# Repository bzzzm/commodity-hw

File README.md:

# Commodity - Board

This project requires Kicad 5.1. It should include everything required to order
the board and assemble it (PCBA).

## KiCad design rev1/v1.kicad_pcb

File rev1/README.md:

# Commodity v1 - rev1

## MCU - STM32F405

  - [Datasheet](https://www.st.com/resource/en/reference_manual/dm00031020-stm32f405-415-stm32f407-417-stm32f427-437-and-stm32f429-439-advanced-arm-based-32-bit-mcus-stmicroelectronics.pdf)
  - based on Phil's design: https://www.youtube.com/watch?v=t5phi3nT8OU

## Power

### 5V Regulator - TPS62133

  - [Datasheet]()
  - [Webench design]()
  
### 3.3V LDO - AMS1117

  - [Datasheet]()

## Sensors
All sensors are connected to `I2C1` on the MCU.

### 9 Axis IMU - BMX055

  - [Datasheet](https://www.bosch-sensortec.com/media/boschsensortec/downloads/datasheets/bst-bmx055-ds000.pdf)
  - I2C addresses:
    - Accelerometer: `0x18`
    - Gyroscope: `0x68`
    - Magnetometer: `0x10`

Connected over I2C, due to some reflow issues the Magnetometer on all (that I tested) my boards is not working.

### Environment sensor - BME280

  - [Datasheet](https://ae-bst.resource.bosch.com/media/_tech/media/datasheets/BST-BME280-DS002.pdf)
  - I2C address: `0x76`

### Current sensor - INA219

  - [Datasheet](https://www.ti.com/lit/ds/symlink/ina219.pdf)
  - I2C address: `0x40`

## Peripherials

### Motor Drivers - 2 x DRV8835

  - [Datasheet](https://www.ti.com/lit/ds/symlink/drv8835.pdf)
  - `MOT_R` for right motors, `MOT_L` for left motors
    
@todo:
  - connected pins
  - PWM, max voltage etc
  - driver modes and the solder point on the back of the board

### TOF Sensors - 2 x VL53L0X

  - [Datasheet]()
  - `TOF_F` for the sensor in the front bumper
  - `TOF_T` for the sensor attached to the RPI camera
  
### Wifi Scanner - ESP8266-01
This scanner will help with positioning data (besides images from RPI cam). 
Small Arduino firmware that will scan for `N` known wifi networks every `X` seconds and will send 
the `RSSI` value via UART. The MCU will make use of DMA to receive the data on `UART2`. Firmware can be found [@todo]().

### RGB Lights - WS2812

  - [Datasheet](https://cdn-shop.adafruit.com/datasheets/WS2812B.pdf)
  - Uses SPI3 MOSI pin on the MCU to send data to the leds

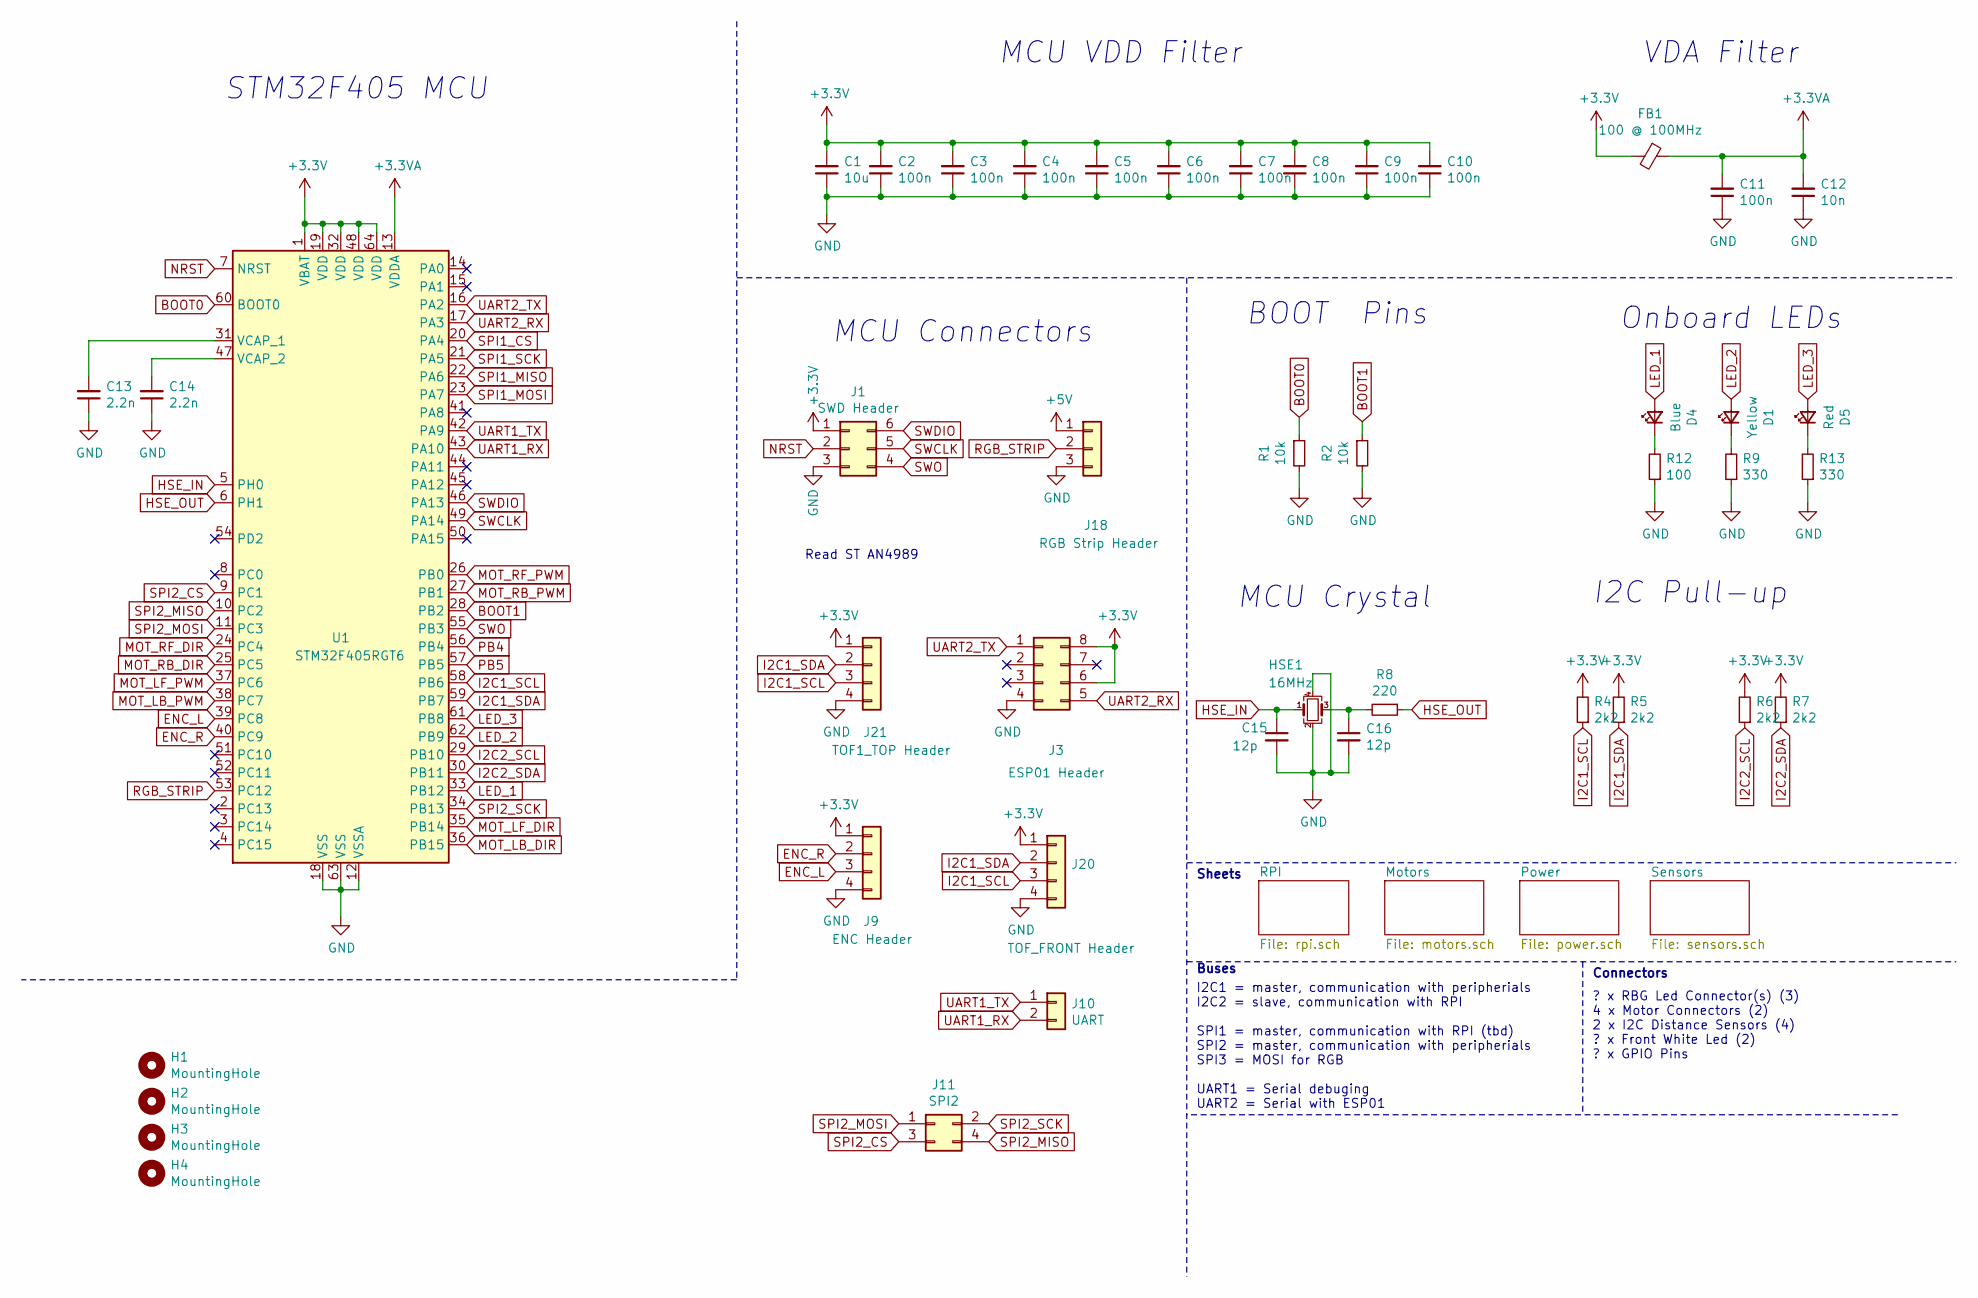
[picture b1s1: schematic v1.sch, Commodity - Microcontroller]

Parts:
C1: 10u; C_0603_1608Metric; LCSC C19702
C2, C3, C4, C5, C6, C7, C8, C9, C10, C11: 100n; C_0402_1005Metric; LCSC C1525
C12: 10n; C_0402_1005Metric; LCSC C15195
C13, C14: 2.2n; C_0603_1608Metric; LCSC C1604
C15, C16: 12p; C_0402_1005Metric; LCSC C1547
D1: Yellow; LED_0603_1608Metric; LCSC C72038
D4: Blue; LED_0603_1608Metric; LCSC C72041
D5: Red; LED_0603_1608Metric; LCSC C2286
FB1: 100 @ 100MHz; R_0805_2012Metric; LCSC C1015
H1, H2, H3, H4: MountingHole; MountingHole_2.7mm_M2.5
HSE1: 16MHz; Crystal_SMD_3225-4Pin_3.2x2.5mm; LCSC C13738
J1: SWD Header; PinHeader_2x03_P2.54mm_Vertical
J3: ESP01 Header; PinSocket_2x04_P2.54mm_Vertical
J9: ENC Header; Molex_PicoBlade_53048-0410_1x04_P1.25mm_Horizontal; Farnell 2779802
J10: UART; PinHeader_1x02_P2.54mm_Vertical
J11: SPI2; PinHeader_2x02_P2.54mm_Vertical
J18: RGB Strip Header; Molex_PicoBlade_53048-0310_1x03_P1.25mm_Horizontal; Farnell 9732918
J20: TOF_FRONT Header; Molex_PicoBlade_53048-0410_1x04_P1.25mm_Horizontal; Farnell 2779802
J21: TOF1_TOP Header; Molex_PicoBlade_53048-0410_1x04_P1.25mm_Horizontal; Farnell 2779802
R1, R2: 10k; R_0402_1005Metric; LCSC C25744
R4, R5, R6, R7: 2k2; R_0402_1005Metric; LCSC C25879
R8: 220; R_0402_1005Metric; LCSC C25091
R9, R13: 330; R_0603_1608Metric; LCSC C23138
R12: 100; R_0603_1608Metric; LCSC C22775
U1: STM32F405RGT6; LQFP-64_10x10mm_P0.5mm; LCSC C15742

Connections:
+3.3VA: C11.2, C12.2, FB1.1, U1.13 (VDDA)
BOOT0: R1.1, U1.60 (BOOT0)
BOOT1: R2.1, U1.28 (PB2)
ENC_L: J9.3, U1.39 (PC8)
ENC_R: J9.2, U1.40 (PC9)
GND: C1.1, C2.1, C3.1, C4.1, C5.1, C6.1, C7.1, C8.1, C9.1, C10.1, C11.1, C12.1, C13.1, C14.1, C15.2, C16.2, HSE1.2, HSE1.4, J1.3, J3.4, J9.4, J18.3, J20.4, J21.4, R1.2, R2.2, R9.1, R12.1, R13.1, U1.12 (VSSA), U1.18 (VSS), U1.63 (VSS); also elsewhere on the board
HSE_IN: C15.1, HSE1.1, U1.5 (PH0)
HSE_OUT: R8.1, U1.6 (PH1)
I2C1_SCL: J20.3, J21.3, R4.1, U1.58 (PB6); also elsewhere on the board
I2C1_SDA: J20.2, J21.2, R5.1, U1.59 (PB7); also elsewhere on the board
I2C2_SCL: R6.1, U1.29 (PB10); also elsewhere on the board
I2C2_SDA: R7.1, U1.30 (PB11); also elsewhere on the board
LED_1: D4.2 (A), U1.33 (PB12)
LED_2: D1.2 (A), U1.62 (PB9)
LED_3: D5.2 (A), U1.61 (PB8)
MOT_LB_DIR: U1.36 (PB15); also elsewhere on the board
MOT_LB_PWM: U1.38 (PC7); also elsewhere on the board
MOT_LF_DIR: U1.35 (PB14); also elsewhere on the board
MOT_LF_PWM: U1.37 (PC6); also elsewhere on the board
MOT_RB_DIR: U1.25 (PC5); also elsewhere on the board
MOT_RB_PWM: U1.27 (PB1); also elsewhere on the board
MOT_RF_DIR: U1.24 (PC4); also elsewhere on the board
MOT_RF_PWM: U1.26 (PB0); also elsewhere on the board
NRST: J1.2, U1.7 (NRST)
unnamed: C13.2, U1.31 (VCAP_1)
unnamed: C14.2, U1.47 (VCAP_2)
unnamed: C16.1, HSE1.3, R8.2
unnamed: D1.1 (K), R9.2
unnamed: D4.1 (K), R12.2
unnamed: D5.1 (K), R13.2
PB4: U1.56 (PB4)
PB5: U1.57 (PB5)
RGB_STRIP: J18.2, U1.53 (PC12)
SPI1_CS: U1.20 (PA4)
SPI1_MISO: U1.22 (PA6); also elsewhere on the board
SPI1_MOSI: U1.23 (PA7); also elsewhere on the board
SPI1_SCK: U1.21 (PA5); also elsewhere on the board
SPI2_CS: J11.3, U1.9 (PC1)
SPI2_MISO: J11.4, U1.10 (PC2)
SPI2_MOSI: J11.1, U1.11 (PC3)
SPI2_SCK: J11.2, U1.34 (PB13)
SWCLK: J1.5, U1.49 (PA14)
SWDIO: J1.6, U1.46 (PA13)
SWO: J1.4, U1.55 (PB3)
TPS_VOS: J18.1; also elsewhere on the board
UART1_RX: J10.2, U1.43 (PA10)
UART1_TX: J10.1, U1.42 (PA9)
UART2_RX: J3.5, U1.17 (PA3)
UART2_TX: J3.1, U1.16 (PA2)

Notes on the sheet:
I2C1 = master, communication with peripherials I2C2 = slave, communication with RPI SPI1 = master, communication with RPI (tbd) SPI2 = master, communication with peripherials SPI3 = MOSI for RGB UART1 = Serial debuging UART2 = Serial with ESP01
MCU VDD Filter
VDA Filter
BOOT Pins
MCU Crystal
MCU Connectors
I2C Pull-up
? x RBG Led Connector(s) (3) 4 x Motor Connectors (2) 2 x I2C Distance Sensors (4) ? x Front White Led (2) ? x GPIO Pins
Buses
Connectors
Sheets
Read ST AN4989
STM32F405 MCU
Onboard LEDs

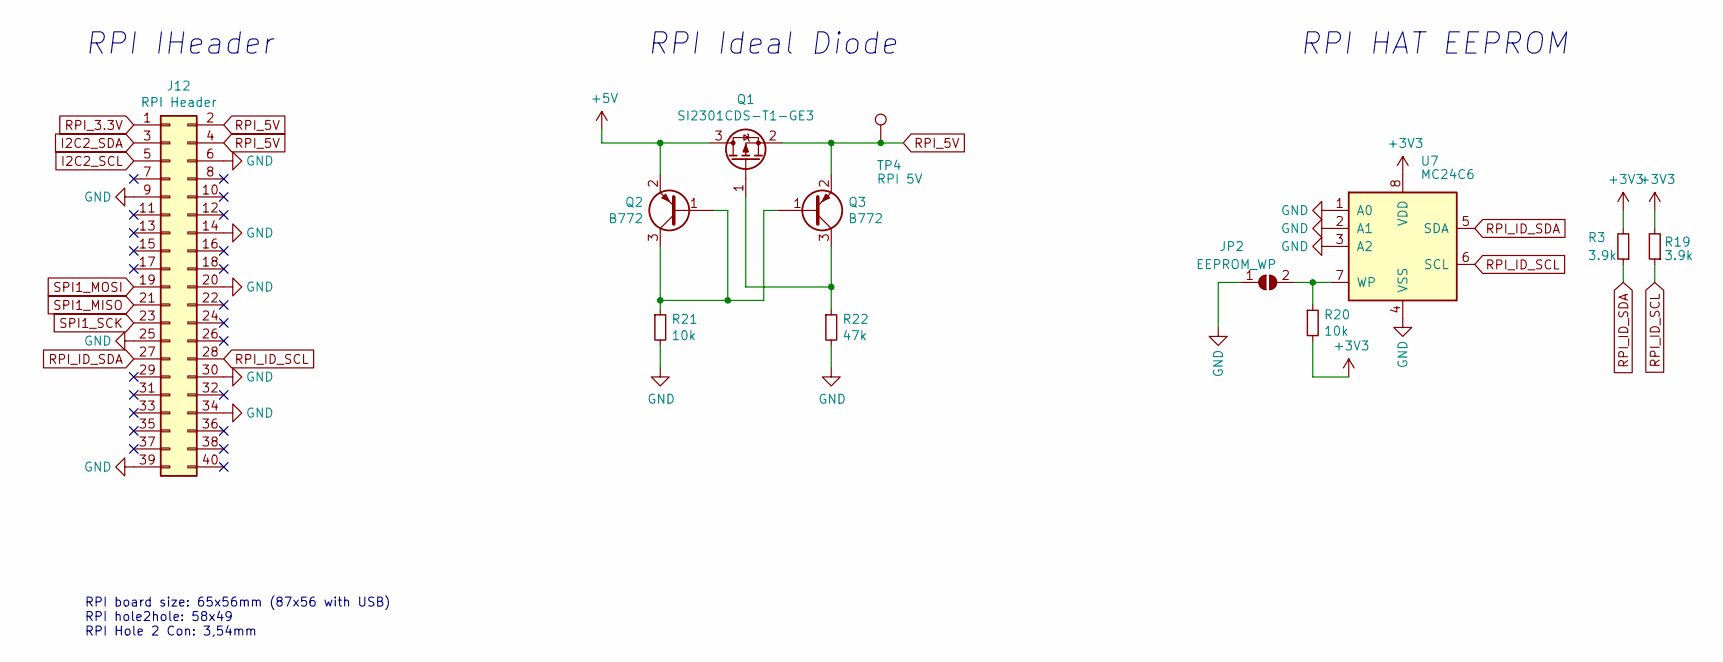
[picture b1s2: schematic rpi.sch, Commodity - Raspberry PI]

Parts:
J12: RPI Header; PinSocket_2x20_P2.54mm_Vertical
JP2: EEPROM_WP; SolderJumper-2_P1.3mm_Open_RoundedPad1.0x1.5mm
Q1: SI2301CDS-T1-GE3; SOT-23; LCSC C10487
Q2, Q3: B772; SOT-89-3; LCSC C24278
R3, R19: 3.9k; R_0402_1005Metric; LCSC C51721
R20: 10k; R_0402_1005Metric; LCSC C25744
R21: 10k; R_0603_1608Metric; LCSC C25804
R22: 47k; R_0603_1608Metric; LCSC C25819
TP4: RPI 5V; TestPoint_Pad_D1.0mm
U7: MC24C6; SOIC-8_3.9x4.9mm_P1.27mm; LCSC C79988

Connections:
GND: J12.6, J12.9, J12.14, J12.20, J12.25, J12.30, J12.34, J12.39, JP2.1 (A), R21.2, R22.2, U7.1 (A0), U7.2 (A1), U7.3 (A2), U7.4 (VSS); also elsewhere on the board
I2C2_SCL: J12.5; also elsewhere on the board
I2C2_SDA: J12.3; also elsewhere on the board
unnamed: JP2.2 (B), R20.1, U7.7 (WP)
unnamed: Q1.1 (G), Q3.3 (C), R22.1
unnamed: Q2.1 (B), Q2.3 (C), Q3.1 (B), R21.1
RPI_3.3V: J12.1
RPI_5V: J12.2, J12.4, Q1.2 (S), Q3.2 (E), TP4.1
RPI_ID_SCL: J12.28, R19.1, U7.6 (SCL)
RPI_ID_SDA: J12.27, R3.1, U7.5 (SDA)
SPI1_MISO: J12.21; also elsewhere on the board
SPI1_MOSI: J12.19; also elsewhere on the board
SPI1_SCK: J12.23; also elsewhere on the board
TPS_VOS: Q1.3 (D), Q2.2 (E); also elsewhere on the board

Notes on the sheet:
RPI board size: 65x56mm (87x56 with USB) RPI hole2hole: 58x49 RPI Hole 2 Con: 3,54mm
RPI Ideal Diode
RPI IHeader
RPI HAT EEPROM

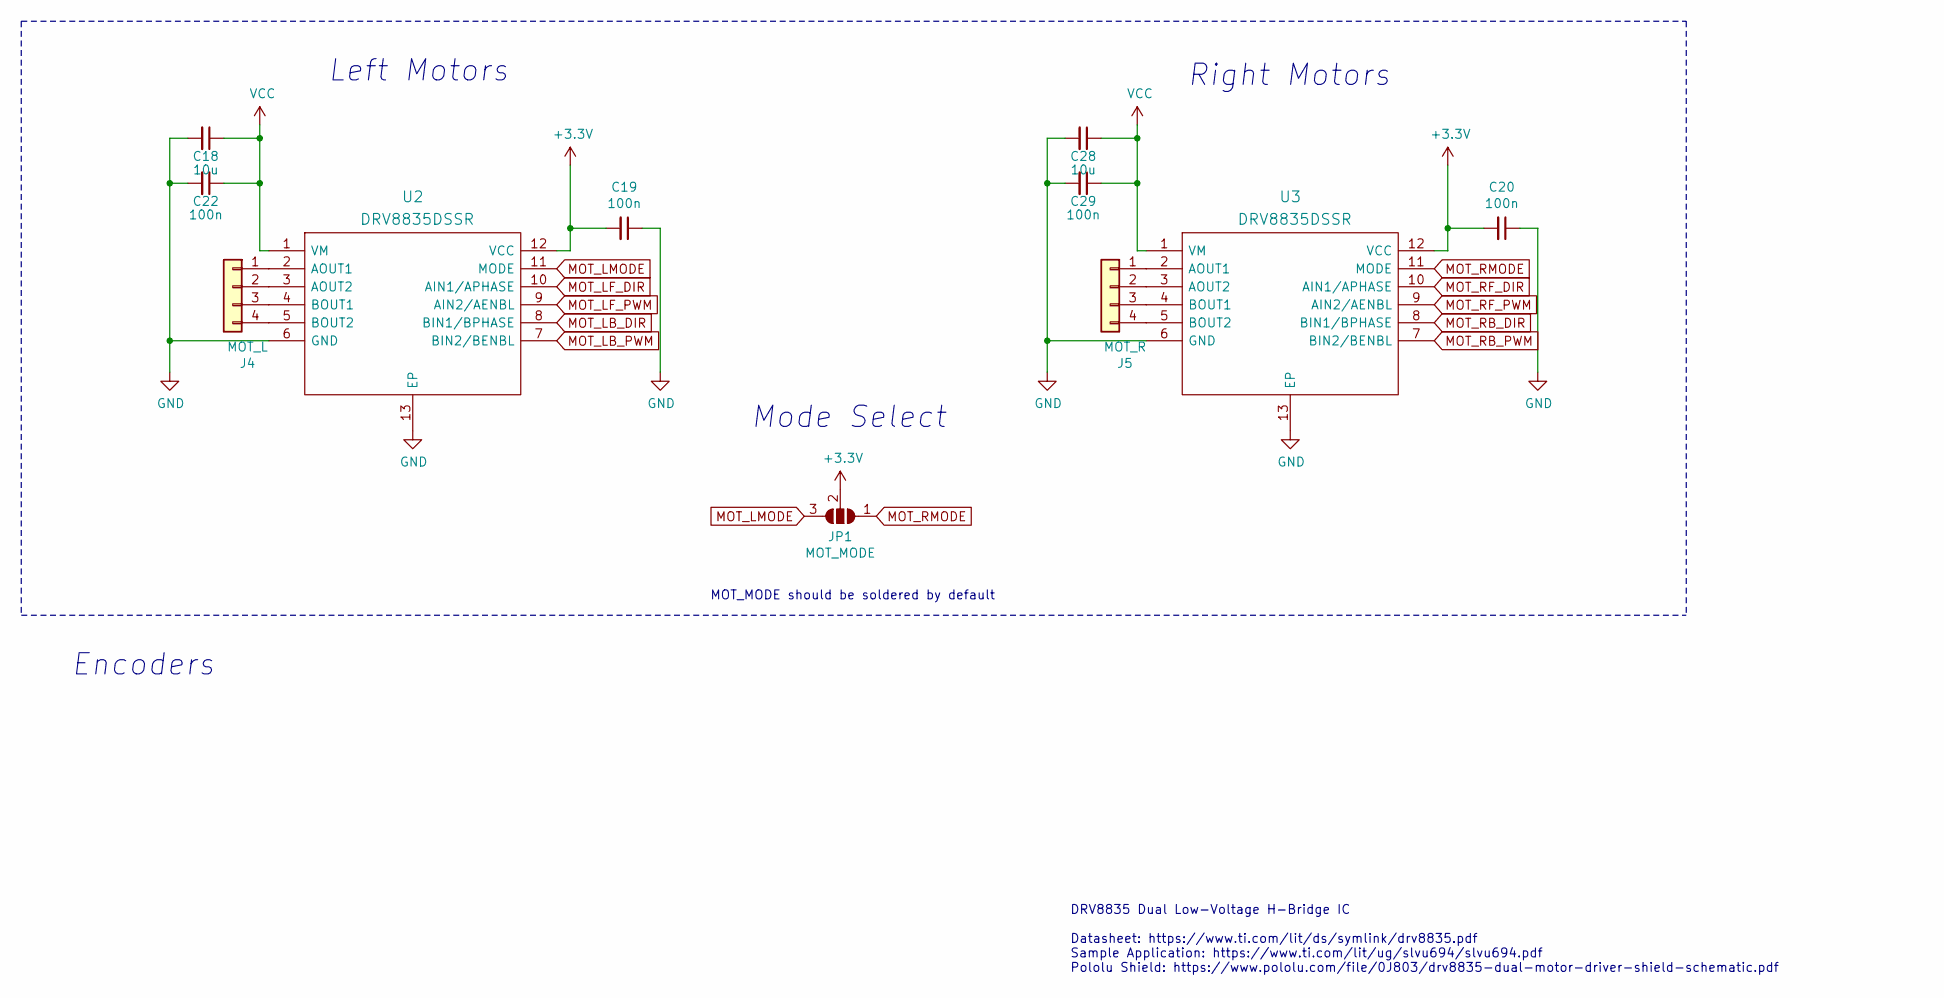
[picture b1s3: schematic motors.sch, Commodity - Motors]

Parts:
C18, C28: 10u; C_1206_3216Metric; LCSC C13585
C19, C20, C22, C29: 100n; C_0603_1608Metric; LCSC C14663
J4: MOT_L; Molex_PicoBlade_53048-0410_1x04_P1.25mm_Horizontal; Farnell 2779802
J5: MOT_R; Molex_PicoBlade_53048-0410_1x04_P1.25mm_Horizontal; Farnell 2779802
JP1: MOT_MODE; SolderJumper-3_P1.3mm_Open_RoundedPad1.0x1.5mm
U2, U3: DRV8835DSSR; SON50P200X300X80-13N; LCSC C129328

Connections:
GND: C18.2, C19.1, C20.1, C22.2, C28.2, C29.2, U2.6 (GND), U2.13 (EP), U3.6 (GND), U3.13 (EP); also elsewhere on the board
INA_VIN-: C18.1, C22.1, C28.1, C29.1, U2.1 (VM), U3.1 (VM); also elsewhere on the board
MOT_LB_DIR: U2.8 (BIN1/BPHASE); also elsewhere on the board
MOT_LB_PWM: U2.7 (BIN2/BENBL); also elsewhere on the board
MOT_LF_DIR: U2.10 (AIN1/APHASE); also elsewhere on the board
MOT_LF_PWM: U2.9 (AIN2/AENBL); also elsewhere on the board
MOT_LMODE: JP1.3 (B), U2.11 (MODE)
MOT_RB_DIR: U3.8 (BIN1/BPHASE); also elsewhere on the board
MOT_RB_PWM: U3.7 (BIN2/BENBL); also elsewhere on the board
MOT_RF_DIR: U3.10 (AIN1/APHASE); also elsewhere on the board
MOT_RF_PWM: U3.9 (AIN2/AENBL); also elsewhere on the board
MOT_RMODE: JP1.1 (A), U3.11 (MODE)
unnamed: J4.1, U2.2 (AOUT1)
unnamed: J4.2, U2.3 (AOUT2)
unnamed: J4.3, U2.4 (BOUT1)
unnamed: J4.4, U2.5 (BOUT2)
unnamed: J5.1, U3.2 (AOUT1)
unnamed: J5.2, U3.3 (AOUT2)
unnamed: J5.3, U3.4 (BOUT1)
unnamed: J5.4, U3.5 (BOUT2)

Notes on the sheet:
Right Motors
Left Motors
Encoders
DRV8835 Dual Low-Voltage H-Bridge IC Datasheet: https://www.ti.com/lit/ds/symlink/drv8835.pdf Sample Application: https://www.ti.com/lit/ug/slvu694/slvu694.pdf Pololu Shield: https://www.pololu.com/file/0J803/drv8835-dual-motor-driver-shield-schematic.pdf
Mode Select
MOT_MODE should be soldered by default

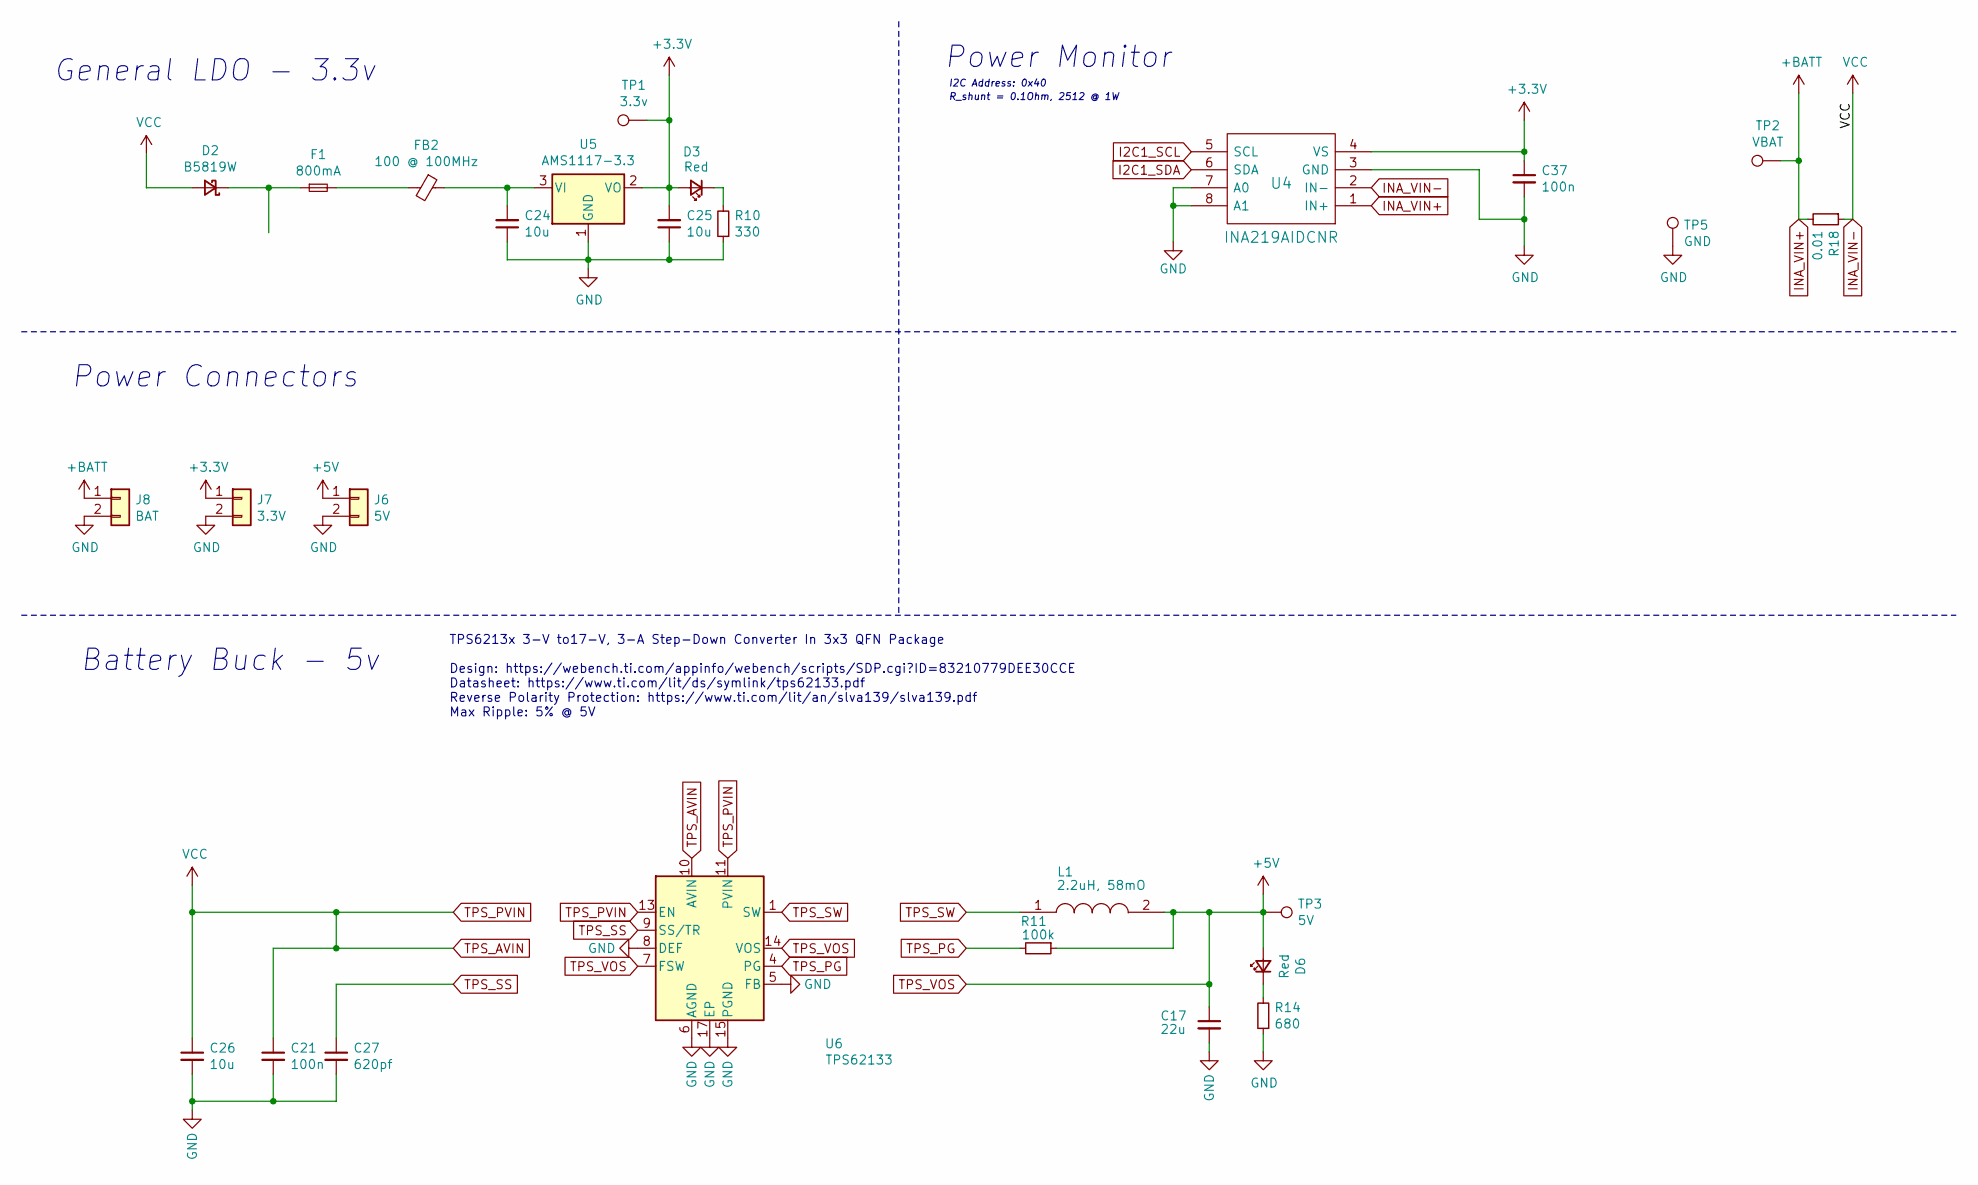
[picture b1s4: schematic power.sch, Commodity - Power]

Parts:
C17: 22u; C_0805_2012Metric; LCSC C45783
C21, C37: 100n; C_0603_1608Metric; LCSC C14663
C24, C25, C26: 10u; C_0805_2012Metric; LCSC C15850
C27: 620pf; C_0603_1608Metric_Pad1.05x0.95mm_HandSolder; Farnell 2819768
D2: B5819W; D_SOD-123; LCSC C8598
D3, D6: Red; LED_0603_1608Metric; LCSC C2286
F1: 800mA; R_1206_3216Metric_Pad1.42x1.75mm_HandSolder; Farnell 2291894
FB2: 100 @ 100MHz; R_0805_2012Metric; LCSC C1015
J6: 5V; PinHeader_1x02_P2.54mm_Vertical
J7: 3.3V; PinHeader_1x02_P2.54mm_Vertical
J8: BAT; JST_XH_S2B-XH-A_1x02_P2.50mm_Horizontal; Farnell 1516289
L1: 2.2uH, 58mO; INDPM4442X200N; LCSC C408335
R10: 330; R_0603_1608Metric; LCSC C23138
R11: 100k; R_0402_1005Metric; LCSC C25741
R14: 680; R_0603_1608Metric; LCSC C23228
R18: 0.01; R_2512_6332Metric_Pad1.52x3.35mm_HandSolder; Farnell 1435952RL
TP1: 3.3v; TestPoint_Pad_D1.0mm
TP2: VBAT; TestPoint_Pad_D1.0mm
TP3: 5V; TestPoint_Pad_D1.0mm
TP5: GND; TestPoint_Pad_D1.0mm
U4: INA219AIDCNR; SOT-23-8; LCSC C87469
U5: AMS1117-3.3; SOT-223-3_TabPin2; LCSC C6186
U6: TPS62133; VQFN-16-1EP_3x3mm_P0.5mm_EP1.68x1.68mm_ThermalVias; LCSC C73973

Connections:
GND: C17.2, C21.2, C24.1, C25.1, C26.2, C27.2, C37.2, J6.2, J7.2, J8.2, R10.1, R14.1, TP5.1, U4.3 (GND), U4.7 (A0), U4.8 (A1), U5.1 (GND), U6.5 (FB), U6.6 (AGND), U6.8 (DEF), U6.15 (PGND), U6.16 (PGND), U6.17 (EP); also elsewhere on the board
I2C1_SCL: U4.5 (SCL); also elsewhere on the board
I2C1_SDA: U4.6 (SDA); also elsewhere on the board
INA_VIN+: J8.1, R18.2, TP2.1, U4.1 (IN+)
INA_VIN-: C21.1, C26.1, D2.2 (A), R18.1, U4.2 (IN-), U6.10 (AVIN), U6.11 (PVIN), U6.12 (PVIN), U6.13 (EN); also elsewhere on the board
unnamed: C24.2, FB2.1, U5.3 (VI)
unnamed: D2.1 (K), F1.1
unnamed: D3.1 (K), R10.2
unnamed: D6.1 (K), R14.2
unnamed: F1.2, FB2.2
TPS_PG: R11.2, U6.4 (PG)
TPS_SS: C27.1, U6.9 (SS/TR)
TPS_SW: L1.1, U6.1 (SW), U6.2 (SW), U6.3 (SW)
TPS_VOS: C17.1, D6.2 (A), J6.1, L1.2, R11.1, TP3.1, U6.7 (FSW), U6.14 (VOS); also elsewhere on the board

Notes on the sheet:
Battery Buck - 5v
Power Connectors
Power Monitor
TPS6213x 3-V to17-V, 3-A Step-Down Converter In 3x3 QFN Package Design: https://webench.ti.com/appinfo/webench/scripts/SDP.cgi?ID=83210779DEE30CCE Datasheet: https://www.ti.com/lit/ds/symlink/tps62133.pdf Reverse Polarity Protection: https://www.ti.com/lit/an/slva139/slva139.pdf Max Ripple: 5% @ 5V
General LDO - 3.3v
I2C Address: 0x40
R_shunt = 0.1Ohm, 2512 @ 1W

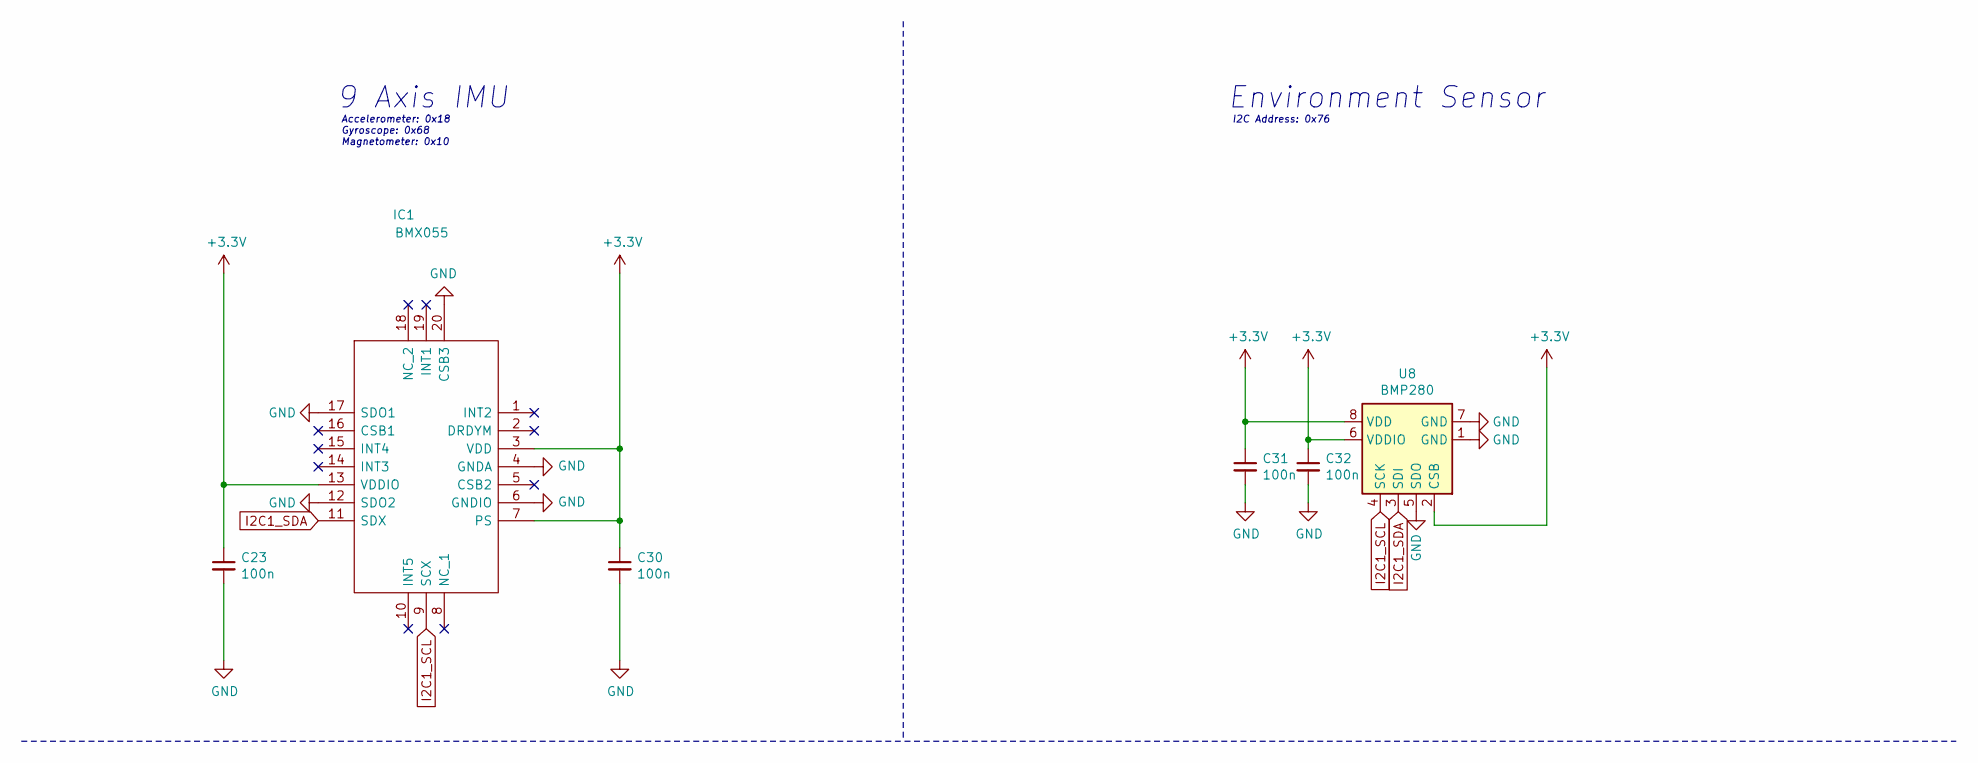
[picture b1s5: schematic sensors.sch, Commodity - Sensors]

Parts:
C23, C30, C31, C32: 100n; C_0603_1608Metric; LCSC C14663
IC1: BMX055; LGA_PACKAGE_20_PINS; Manufacturer_Part_Number BMX055; Mouser Part Number 262-BMX055
U8: BMP280; Bosch_LGA-8_2x2.5mm_P0.65mm_ClockwisePinNumbering; LCSC C83291

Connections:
GND: C23.2, C30.2, C31.2, C32.2, IC1.4 (GNDA), IC1.6 (GNDIO), IC1.12 (SDO2), IC1.17 (SDO1), IC1.20 (CSB3), U8.1 (GND), U8.5 (SDO), U8.7 (GND); also elsewhere on the board
I2C1_SCL: IC1.9 (SCX), U8.4 (SCK); also elsewhere on the board
I2C1_SDA: IC1.11 (SDX), U8.3 (SDI); also elsewhere on the board

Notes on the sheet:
Accelerometer: 0x18 Gyroscope: 0x68 Magnetometer: 0x10
9 Axis IMU
I2C Address: 0x76
Environment Sensor

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
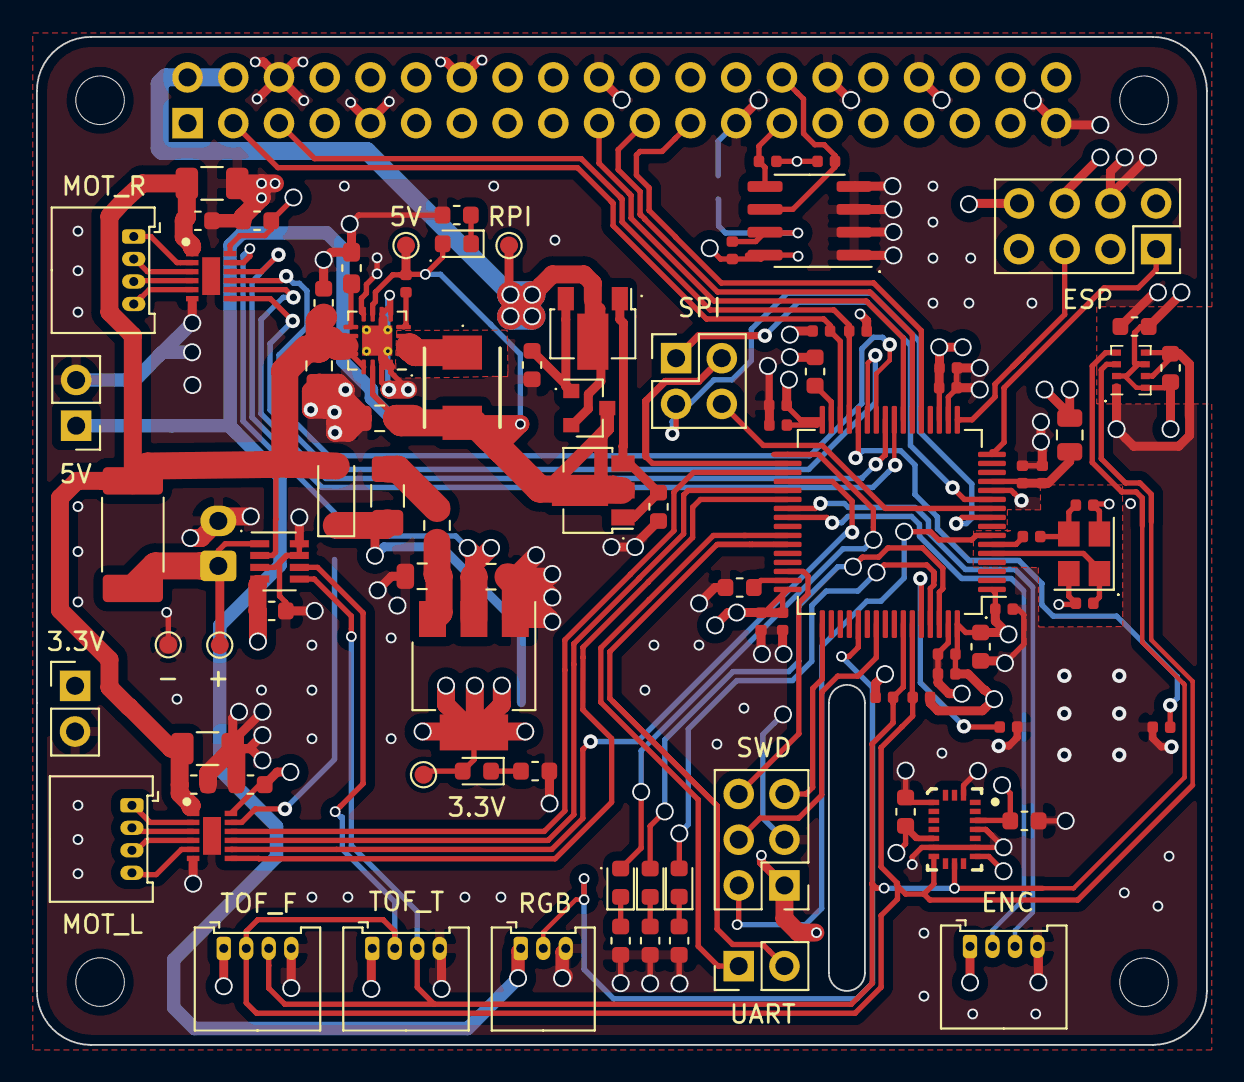
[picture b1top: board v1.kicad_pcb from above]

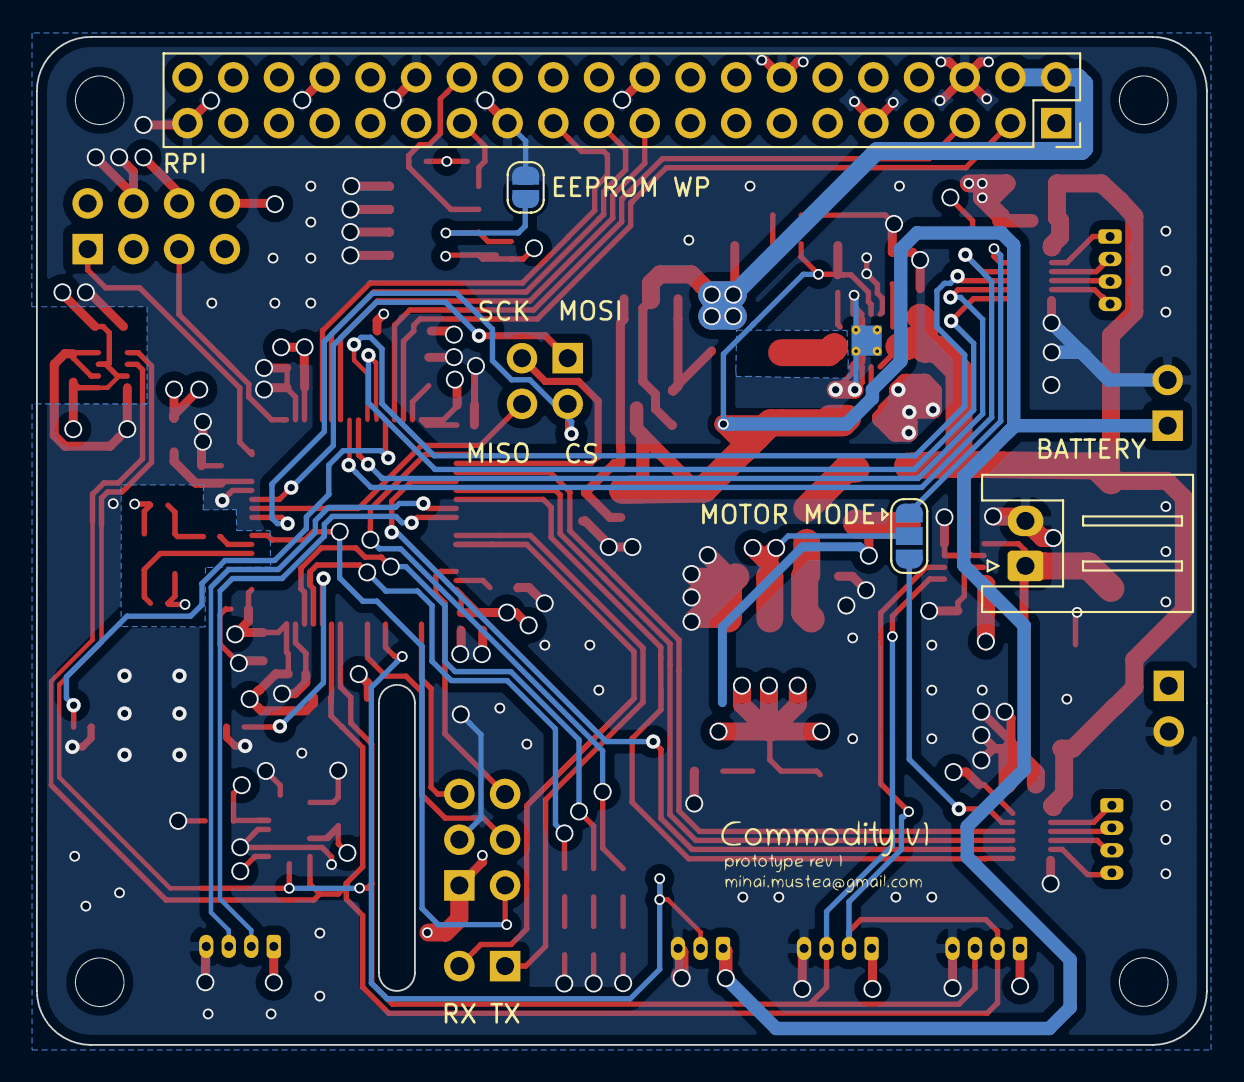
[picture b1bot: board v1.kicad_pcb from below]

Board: 4 copper layers, 65.0 x 56.0 mm, 100 parts (4 on the bottom side), 73 nets.

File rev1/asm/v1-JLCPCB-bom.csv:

Comment,Designator,Quantity,Footprint,LCSC Part #
10u,C1,1,C_0603_1608Metric,C19702
100n,"C2,C3,C4,C5,C6,C7,C8,C9,C10,C11",10,C_0402_1005Metric,C1525
10n,C12,1,C_0402_1005Metric,C15195
2.2n,"C13,C14",2,C_0603_1608Metric,C1604
12p,"C15,C16",2,C_0402_1005Metric,C1547
22u,C17,1,C_0805_2012Metric,C45783
10u,"C18,C28",2,C_1206_3216Metric,C13585
100n,"C19,C20,C21,C22,C23,C29,C30,C31,C32,C37",10,C_0603_1608Metric,C14663
10u,"C24,C25,C26",3,C_0805_2012Metric,C15850
Yellow,D1,1,LED_0603_1608Metric,C72038
B5819W,D2,1,D_SOD-123,C8598
Red,"D3,D5,D6",3,LED_0603_1608Metric,C2286
Blue,D4,1,LED_0603_1608Metric,C72041
100 @ 100MHz,"FB1,FB2",2,R_0805_2012Metric,C1015
16MHz,HSE1,1,Crystal_SMD_3225-4Pin_3.2x2.5mm,C13738
BMX055,IC1,1,LGA_PACKAGE_20_PINS,C94022
"2.2uH, 58mO",L1,1,SMD-PIND-4.2x4.4x2.0_0.8x2.0,C408335
SI2301CDS-T1-GE3,Q1,1,SOT-23,C10487
B772,"Q2,Q3",2,SOT-89-3,C24278
10k,"R1,R2,R20",3,R_0402_1005Metric,C25744
3.9k,"R3,R19",2,R_0402_1005Metric,C51721
2k2,"R4,R5,R6,R7",4,R_0402_1005Metric,C25879
220,R8,1,R_0402_1005Metric,C25091
330,"R9,R10,R13",3,R_0603_1608Metric,C23138
100k,R11,1,R_0402_1005Metric,C25741
100,R12,1,R_0603_1608Metric,C22775
680,R14,1,R_0603_1608Metric,C23228
10k,R21,1,R_0603_1608Metric,C25804
47k,R22,1,R_0603_1608Metric,C25819
STM32F405RGT6,U1,1,LQFP-64_10x10mm_P0.5mm,C15742
DRV8835DSSR,"U2,U3",2,WSON-12_EP_2.0x3.0x0.5P,C129328
INA219AIDCNR,U4,1,SOT-23-8,C87469
AMS1117-3.3,U5,1,SOT-223-3_TabPin2,C6186
TPS62133,U6,1,VQFN-16_EP_3.0x3.0x0.5P,C73973
MC24C6,U7,1,SOIC-8_3.9x4.9mm_P1.27mm,C79988
BMP280,U8,1,Bosch_LGA-8_2x2.5mm_P0.65mm_ClockwisePinNumbering,C83291

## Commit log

2020-09-15 initial github release
2020-09-15 added pdf schematic
2020-09-15 added render screenshots
2020-09-15 more images
